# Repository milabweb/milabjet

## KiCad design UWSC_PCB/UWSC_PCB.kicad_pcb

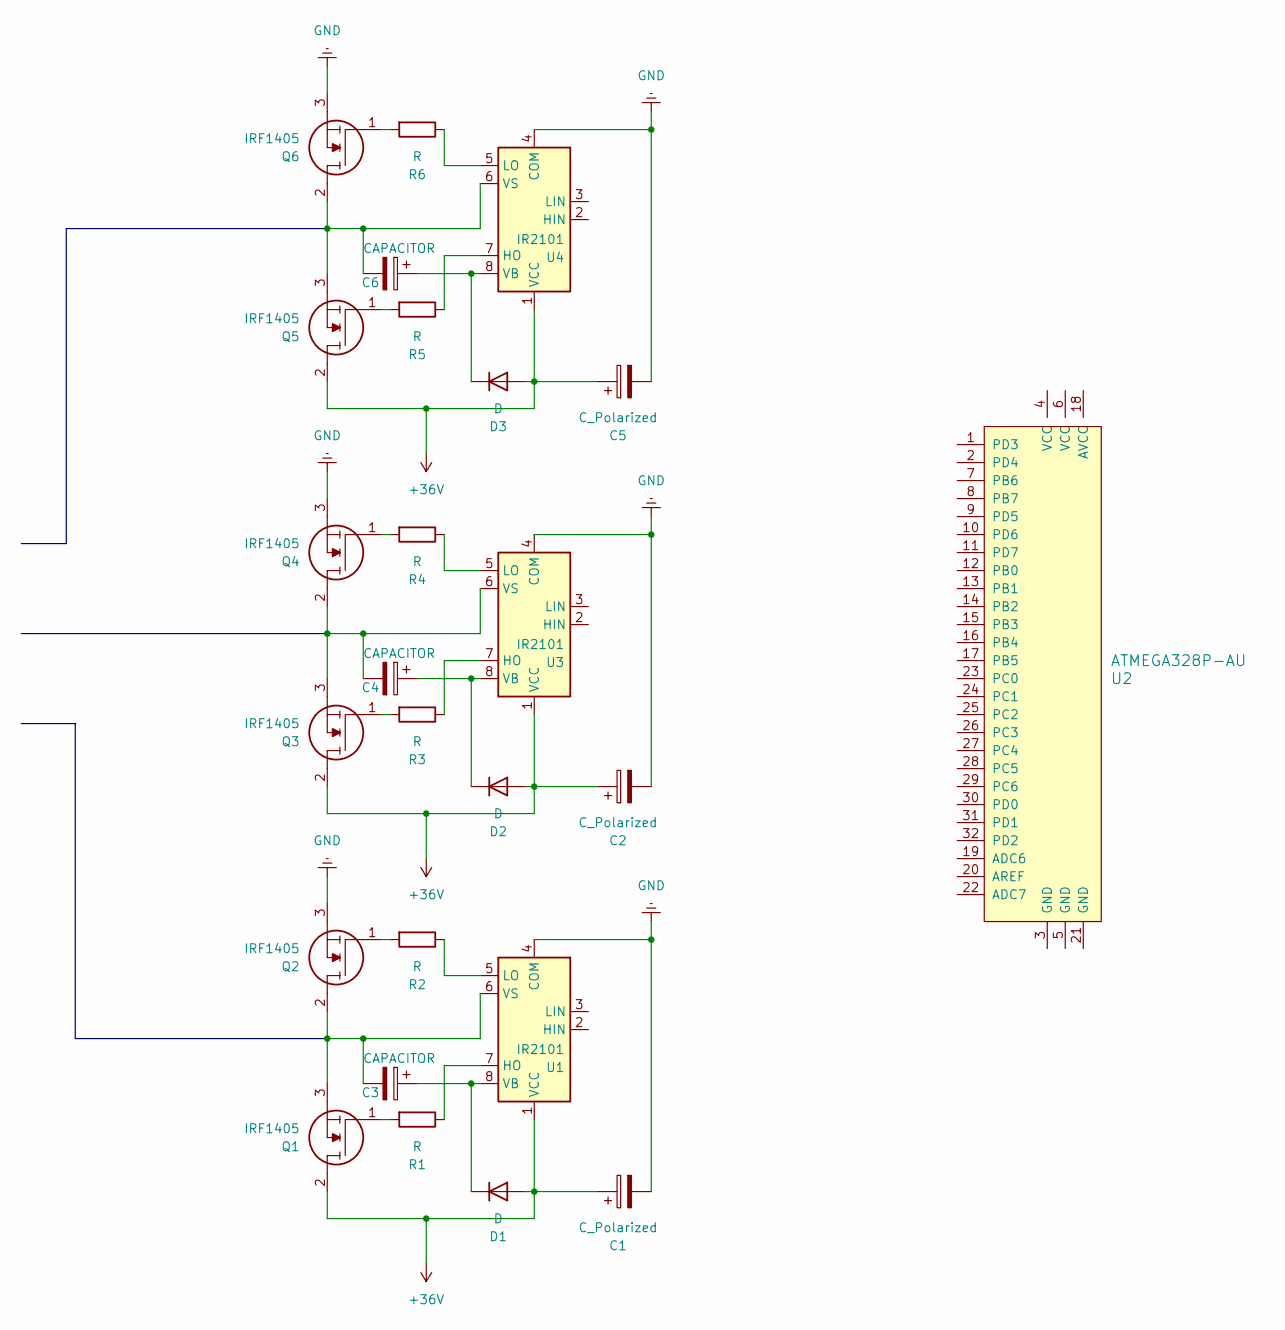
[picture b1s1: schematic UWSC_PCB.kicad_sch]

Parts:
C1, C2, C5: C_Polarized; CP_Radial_D4.0mm_P2.00mm
C3, C4, C6: CAPACITOR; CP_Radial_D4.0mm_P2.00mm
D1, D2, D3: D; D_0201_0603Metric
Q1, Q2, Q3, Q4, Q5, Q6: IRF1405; TO254P483X1016X1994-3P; Manufacturer_Part_Number IRF1405
R1, R2, R3, R4, R5, R6: R; R_0201_0603Metric
U1, U3, U4: IR2101; DIP-8_W7.62mm_SMDSocket_SmallPads
U2: ATMEGA328P-AU; TQFP-32_7x7mm; MPN ATMEGA328P-AU; Digi-Key_PN ATMEGA328P-AU-ND

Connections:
+36V: C1.1, C2.1, C5.1, D1.2 (A), D2.2 (A), D3.2 (A), Q1.2, Q3.2, Q5.2, U1.1 (VCC), U3.1 (VCC), U4.1 (VCC)
GND: C1.2, C2.2, C5.2, Q2.3, Q4.3, Q6.3, U1.4 (COM), U3.4 (COM), U4.4 (COM)
unnamed: C3.1, D1.1 (K), U1.8 (VB)
unnamed: C4.1, D2.1 (K), U3.8 (VB)
unnamed: C6.1, D3.1 (K), U4.8 (VB)
unnamed: Q1.1, R1.2
unnamed: Q2.1, R2.2
unnamed: Q3.1, R3.2
unnamed: Q4.1, R4.2
unnamed: Q5.1, R5.2
unnamed: Q6.1, R6.2
unnamed: R1.1, U1.7 (HO)
unnamed: R2.1, U1.5 (LO)
unnamed: C3.2, Q1.3, Q2.2, U1.6 (VS)
unnamed: R3.1, U3.7 (HO)
unnamed: R4.1, U3.5 (LO)
unnamed: C4.2, Q3.3, Q4.2, U3.6 (VS)
unnamed: R5.1, U4.7 (HO)
unnamed: R6.1, U4.5 (LO)
unnamed: C6.2, Q5.3, Q6.2, U4.6 (VS)

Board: 2 copper layers, 25 parts (0 on the bottom side), 20 nets, no tracks yet.

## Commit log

2025-03-08 Add a README.md
2025-03-08 all data
2025-03-09 CAP_2_2_2 eklendi
2025-03-10 CAP_2_1 DE DEĞİŞİKLİK GÖVDEYE GEÇME ESNASINDA FLANŞ ZORLANMASIN DİYE 0.5 MM İNCELTME YAPILDI VE 70MM GÖVDE GİRİŞİNE 69MM FLANŞ GİRİŞ YAPACAK
2025-03-10 cap_2_2_1 ve cap_2_2_2 modellerinde delikler m3 girişi düzeltildi 3.2mm olarak ayarlandı
2025-04-04 new model add
2025-04-17 solid çizimleri eklendi
2025-04-18 difuser eklendi
2025-04-18 diffuser update
